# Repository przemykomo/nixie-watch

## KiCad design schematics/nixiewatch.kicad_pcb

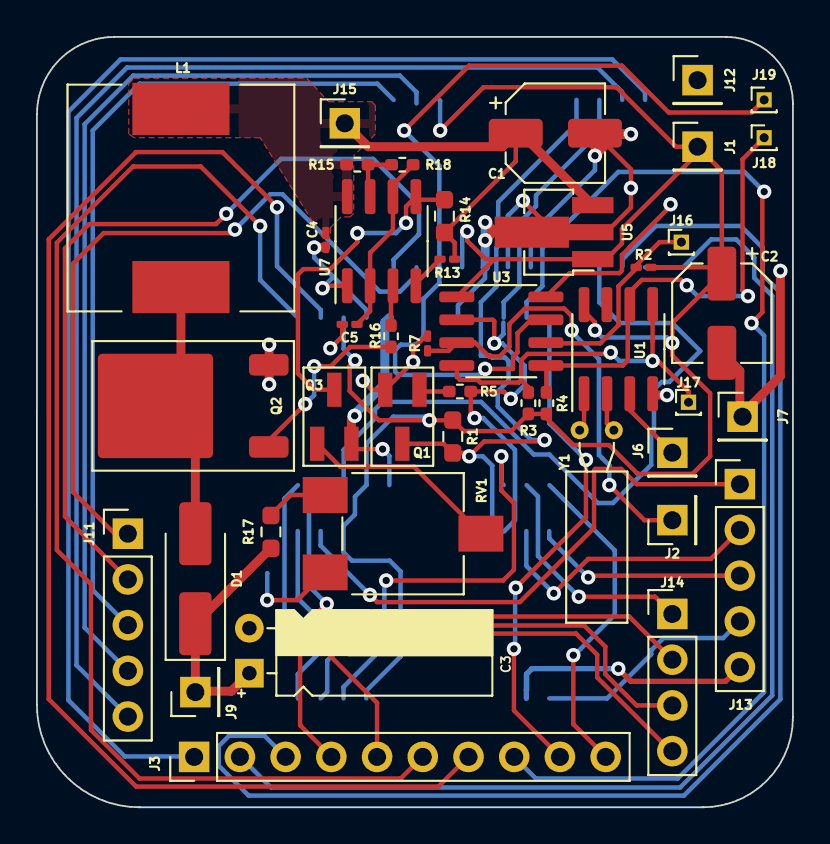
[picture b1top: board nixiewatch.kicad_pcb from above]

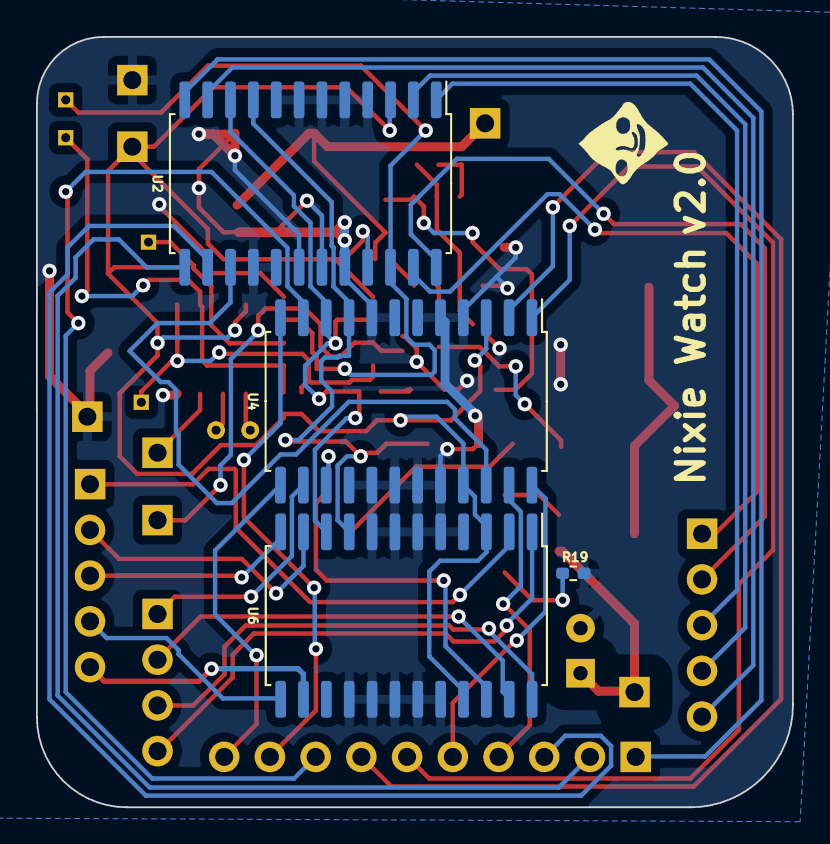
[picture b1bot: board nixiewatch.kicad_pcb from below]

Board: 2 copper layers, 42.0 x 42.8 mm, 47 parts (4 on the bottom side), 51 nets.

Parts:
C1, C2: 33u; CP_Elec_5x5.3
C3: 1u 200V; CP_RADIAL_D5.00mm_P2.50mm_H12.0mm_Horizontal
C4: 100n; C_0201_0603Metric_Pad0.64x0.40mm_HandSolder
C5: 2n2; C_0201_0603Metric_Pad0.64x0.40mm_HandSolder
D1: S1K; D_SMA_Handsoldering
J1, J9: ButtonH; PinHeader_1x01_P2.54mm_Vertical
J2: ButtonL; PinHeader_1x01_P2.54mm_Vertical
J3: Conn_01x10; PinHeader_1x10_P2.54mm_Vertical
J6: BT2_3V; PinHeader_1x01_P2.54mm_Vertical
J7: BT2GND; PinHeader_1x01_P2.54mm_Vertical
J11, J13: Conn_01x05; PinHeader_1x05_P2.54mm_Vertical
J12: BTGND; PinHeader_1x01_P2.54mm_Vertical
J14: Conn_01x04; PinHeader_1x04_P2.54mm_Vertical
J15: BT1_8V; PinHeader_1x01_P2.54mm_Vertical
J16: reset; PinHeader_1x01_P1.00mm_Vertical
J17: mosi; PinHeader_1x01_P1.00mm_Vertical
J18: miso; PinHeader_1x01_P1.00mm_Vertical
J19: sck; PinHeader_1x01_P1.00mm_Vertical
L1: 180u; L_12x12mm_H8mm
Q1, Q3: BC846A; SOT-23_Handsoldering
Q2: WMO10N60C2; TO-252-2
R1, R14: 51k; R_0603_1608Metric_Pad0.98x0.95mm_HandSolder
R2, R7, R13: 20k; R_0201_0603Metric_Pad0.64x0.40mm_HandSolder
R3, R4: 2k2; R_0402_1005Metric_Pad0.72x0.64mm_HandSolder
R5: 6k8; R_0402_1005Metric_Pad0.72x0.64mm_HandSolder
R15: 1k; R_0402_1005Metric_Pad0.72x0.64mm_HandSolder
R16: 100; R_0402_1005Metric_Pad0.72x0.64mm_HandSolder
R17: 680k; R_0603_1608Metric_Pad0.98x0.95mm_HandSolder
R18: 10k; R_0402_1005Metric_Pad0.72x0.64mm_HandSolder
R19: 470; R_0402_1005Metric_Pad0.72x0.64mm_HandSolder
RV1: 5k; Potentiometer_ACP_CA6-VSMD_Vertical
U1: DS1307Z+; SOIC-8_3.9x4.9mm_P1.27mm
U2, U4, U6: TPIC6A595DWR; SOIC-24W_7.5x15.4mm_P1.27mm
U3: ATtiny412-SS; SOIC-8_3.9x4.9mm_P1.27mm
U5: DI78M05UAB; SOT-89-3_Handsoldering
U7: NE555D; SOIC-8_3.9x4.9mm_P1.27mm
Y1: 32.768kHz 12.5pF; Crystal_C38-LF_D3.0mm_L8.0mm_Horizontal

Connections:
+3V0: J6.1, U1.3 (VBAT)
+5V: C2.1, J1.1, R1.2, R2.2, R3.1, R4.1, U1.8 (VCC), U2.3 (~SRCLR), U2.21 (VCC), U3.1 (VCC), U4.3 (~SRCLR), U4.21 (VCC), U5.1 (VO), U6.3 (~SRCLR), U6.21 (VCC)
+170V: C3.1, D1.1 (K), J9.1, R17.1
+BATT: C1.1, C4.1, J15.1, L1.1, R13.1, R14.1, R15.1, U5.3 (VI), U7.8 (VCC)
/170V_int: D1.2 (A), L1.2, Q2.2 (D)
/RCK: Q1.3 (C), R1.1, U2.9 (RCK), U4.9 (RCK), U6.9 (RCK)
/SERIAL_DATA: J19.1, U2.22 (SER_IN), U3.7 (PA3)
/SRCK: R5.2, U2.10 (SRCK), U3.2 (PA6), U4.10 (SRCK), U6.10 (SRCK)
GND: C1.2, C2.2, C3.2, C4.2, C5.2, J7.1, J12.1, Q1.2 (E), Q2.3 (S), Q3.2 (E), R7.1, R19.2, U1.4 (GND), U2.4 (~G), U2.5 (PGND), U2.6 (PGND), U2.7 (PGND), U2.8 (PGND), U2.16 (LGND), U2.17 (PGND), U2.18 (PGND), U2.19 (PGND), U2.20 (PGND), U3.8 (GND), U4.4 (~G), U4.5 (PGND), U4.6 (PGND), U4.7 (PGND), U4.8 (PGND), U4.16 (LGND), U4.17 (PGND), U4.18 (PGND), U4.19 (PGND), U4.20 (PGND), U5.2 (GND), U6.4 (~G), U6.5 (PGND), U6.6 (PGND), U6.7 (PGND), U6.8 (PGND), U6.16 (LGND), U6.17 (PGND), U6.18 (PGND), U6.19 (PGND), U6.20 (PGND), U7.1 (GND)
unnamed: J2.1, R7.2, U3.3 (PA7)
unnamed: J3.1, U2.12 (DRAIN5)
unnamed: J3.2, U2.13 (DRAIN6)
unnamed: J3.3, U2.14 (DRAIN7)
unnamed: J3.4, U4.23 (DRAIN0)
unnamed: J3.5, U4.24 (DRAIN1)
unnamed: J3.6, U4.1 (DRAIN2)
unnamed: J3.7, U4.2 (DRAIN3)
unnamed: J3.8, U4.11 (DRAIN4)
unnamed: J3.9, U4.12 (DRAIN5)
unnamed: J3.10, U4.13 (DRAIN6)
unnamed: J11.1, U2.23 (DRAIN0)
unnamed: J11.2, U2.24 (DRAIN1)
unnamed: J11.3, U2.1 (DRAIN2)
unnamed: J11.4, U2.2 (DRAIN3)
unnamed: J11.5, U2.11 (DRAIN4)
unnamed: J13.1, U6.2 (DRAIN3)
unnamed: J13.2, U6.11 (DRAIN4)
unnamed: J13.3, U6.12 (DRAIN5)
unnamed: J13.4, U6.13 (DRAIN6)
unnamed: J13.5, U6.14 (DRAIN7)
unnamed: J14.1, U4.14 (DRAIN7)
unnamed: J14.2, U6.23 (DRAIN0)
unnamed: J14.3, U6.24 (DRAIN1)
unnamed: J14.4, U6.1 (DRAIN2)
unnamed: J16.1, R2.1, U3.6 (~RESET/PA0)
unnamed: J17.1, R3.2, U1.5 (SDA), U3.4 (PA1)
unnamed: J18.1, R4.2, U1.6 (SCL), U3.5 (PA2)
unnamed: Q1.1 (B), R5.1
unnamed: Q2.1 (G), R16.1
unnamed: Q3.1 (B), RV1.2
unnamed: Q3.3 (C), R14.2, U7.5 (CV)
unnamed: R17.2, RV1.3
unnamed: R19.1, RV1.1
unnamed: U1.1 (X1), Y1.1
unnamed: U1.2 (X2), Y1.2
unnamed: U2.15 (SER_OUT), U4.22 (SER_IN)
unnamed: U4.15 (SER_OUT), U6.22 (SER_IN)
unnamed: R15.2, R18.1, U7.7 (DIS)
unnamed: R16.2, U7.3 (Q)
unnamed: R13.2, U7.4 (R)
unnamed: C5.1, R18.2, U7.2 (TR), U7.6 (THR)

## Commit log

2023-04-09 init
2023-04-16 it's working, reads data from DS1307 properly
2023-04-19 allow user to set time
2023-04-19 pcb layout
2023-04-24 cleaned up the schematic
2023-04-25 updated gitignore
2023-05-18 smd version
2023-06-19 attiny412
2023-08-05 attiny25
2023-12-17 added model and showcase img
2023-12-17 rename README
